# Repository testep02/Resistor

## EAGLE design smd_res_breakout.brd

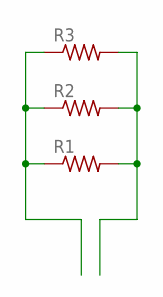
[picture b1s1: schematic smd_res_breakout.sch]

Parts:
R1: R-US_R1206; R1206
R2: R-US_R0805; R0805
R3: R-US_R0603; R0603

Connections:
1: R1.1, R2.1, R3.1
2: R1.2, R2.2, R3.2

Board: 2 copper layers, 3 parts (0 on the bottom side), 2 nets, no tracks yet.

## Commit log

2017-03-01 Initial commit of SMD Resistor Breakout board
